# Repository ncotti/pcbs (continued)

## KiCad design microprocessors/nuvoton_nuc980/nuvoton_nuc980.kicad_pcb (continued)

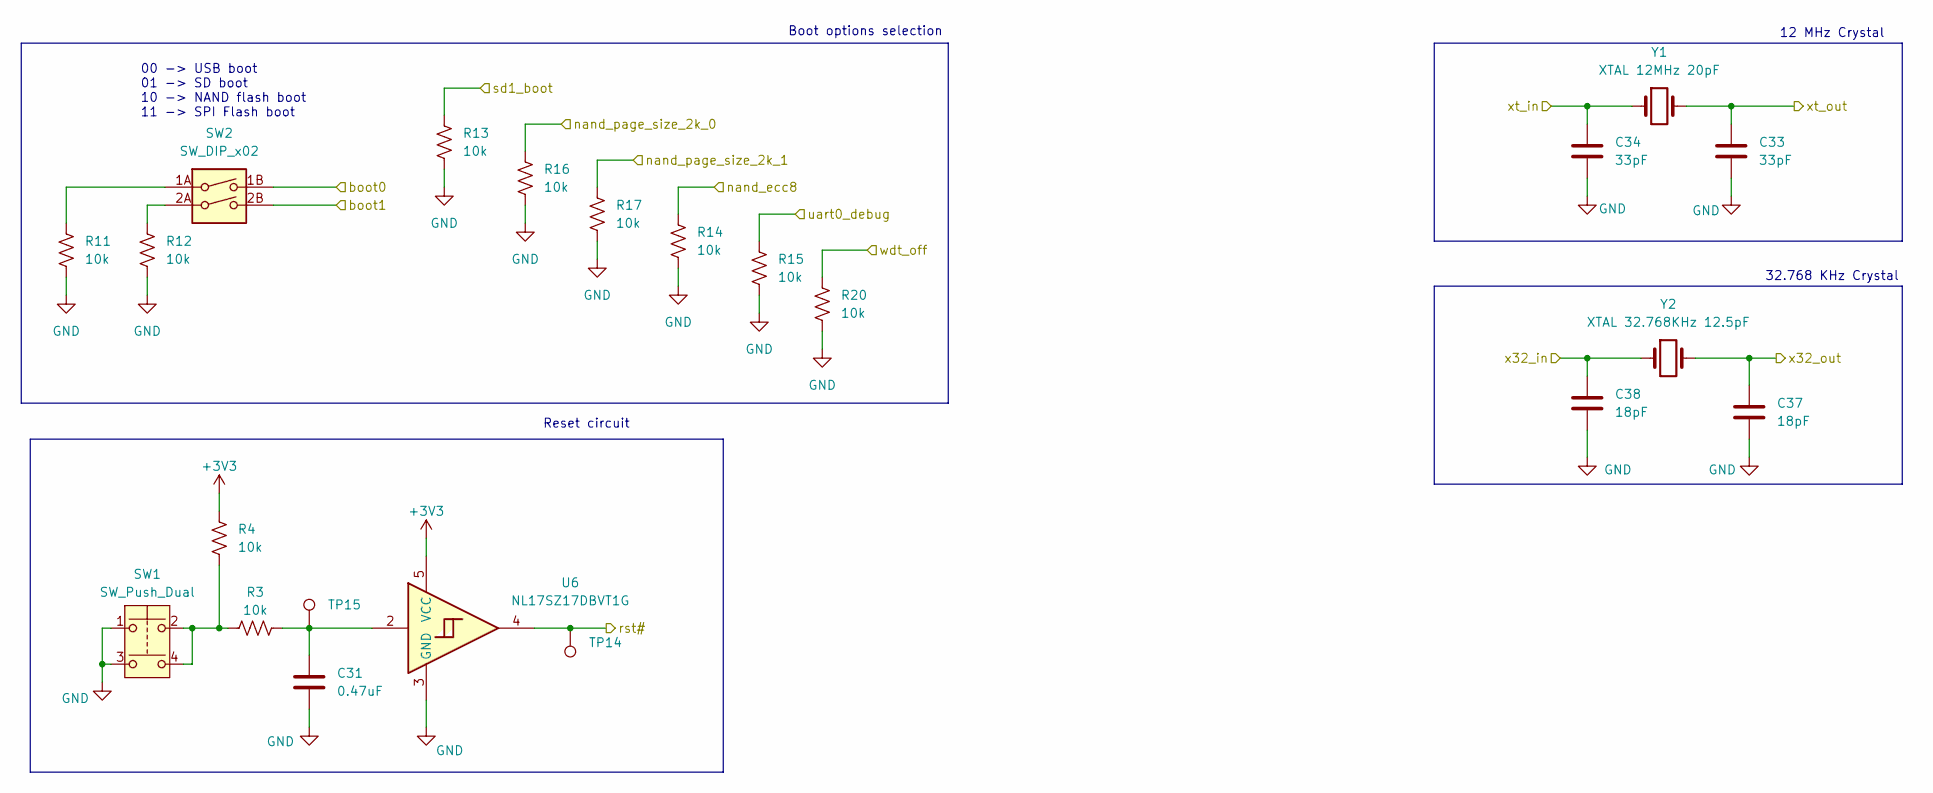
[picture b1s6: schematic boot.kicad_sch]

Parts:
C31: 0.47uF; C_0805_2012Metric_Pad1.18x1.45mm_HandSolder; Mfr. P/N CL21B474KAFNNNG
C33, C34: 33pF; C_0805_2012Metric_Pad1.18x1.45mm_HandSolder; Mfr. P/N CC0805JRNPO9BN330
C37, C38: 18pF; C_0805_2012Metric_Pad1.18x1.45mm_HandSolder; Mfr. P/N CC0805JRNPO9BN180
R3, R4, R11, R12, R13, R14, R15, R16, R17, R20: 10k; R_0805_2012Metric_Pad1.20x1.40mm_HandSolder; Mfr. P/N RC0805FR-1310KL
SW1: SW_Push_Dual; SW_PUSH_6mm_H5mm; Mfr. P/N TS02-66-60-BK-260-SCR-D
SW2: SW_DIP_x02; SW_DS01-254-L-02BE; Mfr. P/N DS01-254-L-02BE
TP14, TP15: TestPoint; TestPoint_Pad_D2.0mm
U6: NL17SZ17DBVT1G; SC-74A-5_1.55x2.9mm_P0.95mm; Mfr. P/N NL17SZ17DBVT1G
Y1: XTAL 12MHz 20pF; Crystal_SMD_HC49-SD_HandSoldering; Mfr. P/N 12M20P2/49SMT
Y2: XTAL 32.768KHz 12.5pF; Crystal_SMD_3215-2Pin_3.2x1.5mm; Mfr. P/N Q 0,032768-JTX310-12,5-20-T2-70K-LF

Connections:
+3V3: R4.1, U6.5 (VCC); also elsewhere on the board
/boot0: SW2.1B; also elsewhere on the board
/boot1: SW2.2B; also elsewhere on the board
/nand_ecc8: R14.1; also elsewhere on the board
/nand_page_size_2k_0: R16.1; also elsewhere on the board
/nand_page_size_2k_1: R17.1; also elsewhere on the board
/rst#: TP14.1, U6.4; also elsewhere on the board
/sd1_boot: R13.1; also elsewhere on the board
/uart0_debug: R15.1; also elsewhere on the board
/wdt_off: R20.1; also elsewhere on the board
/x32_in: C38.1, Y2.1; also elsewhere on the board
/x32_out: C37.1, Y2.2; also elsewhere on the board
/xt_in: C34.1, Y1.1; also elsewhere on the board
/xt_out: C33.1, Y1.2; also elsewhere on the board
GND: C31.2, C33.2, C34.2, C37.2, C38.2, R11.2, R12.2, R13.2, R14.2, R15.2, R16.2, R17.2, R20.2, SW1.1, SW1.3, U6.3 (GND); also elsewhere on the board
unnamed: C31.1, R3.2, TP15.1, U6.2
unnamed: R3.1, R4.2, SW1.2, SW1.4
unnamed: R11.1, SW2.1A
unnamed: R12.1, SW2.2A

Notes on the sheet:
Boot options selection
Reset circuit
00 -> USB boot 01 -> SD boot 10 -> NAND flash boot 11 -> SPI Flash boot
12 MHz Crystal
32.768 KHz Crystal

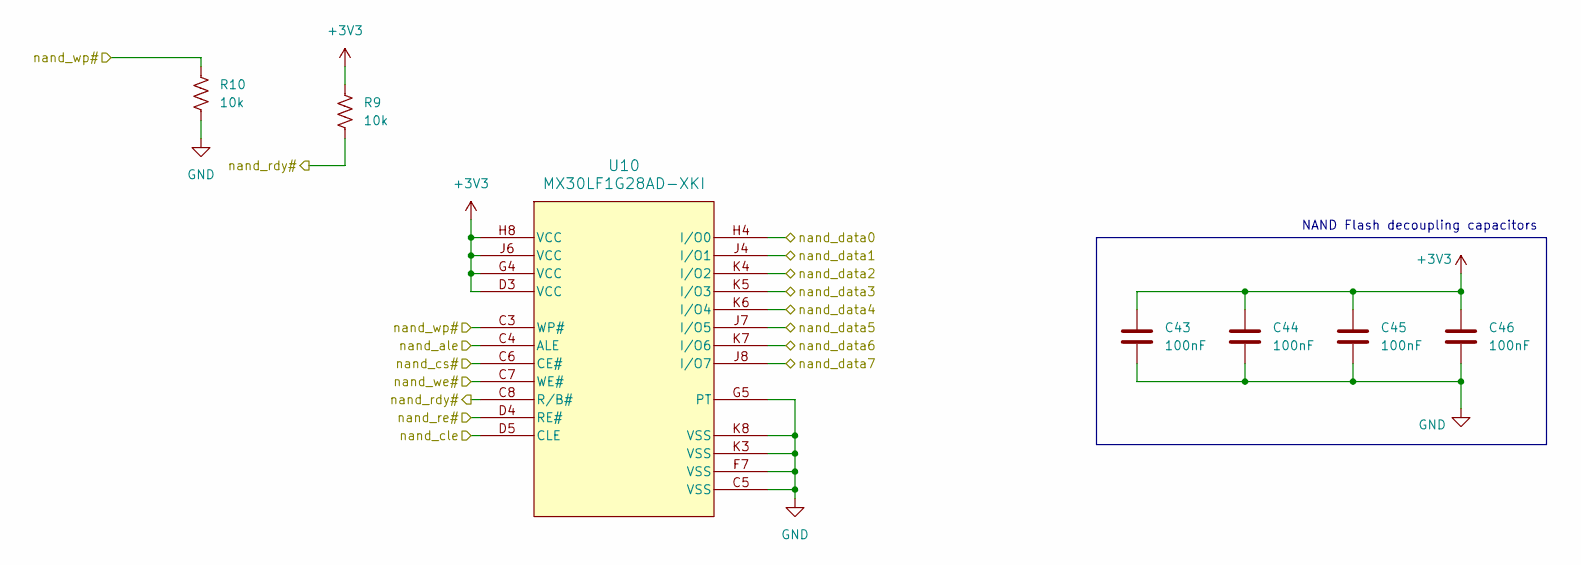
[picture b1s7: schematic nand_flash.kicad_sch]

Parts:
C43, C44, C45, C46: 100nF; C_0805_2012Metric_Pad1.18x1.45mm_HandSolder; Mfr. P/N CL21B104KACNNNC
R9, R10: 10k; R_0805_2012Metric_Pad1.20x1.40mm_HandSolder; Mfr. P/N RC0805FR-1310KL
U10: MX30LF1G28AD-XKI; VFBGA63_9X11_MAC-M; Mfr. P/N MX30LF1G28AD-XKI

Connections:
+3V3: C43.1, C44.1, C45.1, C46.1, R9.1, U10.D3 (VCC), U10.G4 (VCC), U10.H8 (VCC), U10.J6 (VCC); also elsewhere on the board
/nand_ale: U10.C4 (ALE); also elsewhere on the board
/nand_cle: U10.D5 (CLE); also elsewhere on the board
/nand_cs#: U10.C6 (CE#); also elsewhere on the board
/nand_data0: U10.H4 (I/O0); also elsewhere on the board
/nand_data1: U10.J4 (I/O1); also elsewhere on the board
/nand_data2: U10.K4 (I/O2); also elsewhere on the board
/nand_data3: U10.K5 (I/O3); also elsewhere on the board
/nand_data4: U10.K6 (I/O4); also elsewhere on the board
/nand_data5: U10.J7 (I/O5); also elsewhere on the board
/nand_data6: U10.K7 (I/O6); also elsewhere on the board
/nand_data7: U10.J8 (I/O7); also elsewhere on the board
/nand_rdy#: R9.2, U10.C8 (R/B#); also elsewhere on the board
/nand_re#: U10.D4 (RE#); also elsewhere on the board
/nand_we#: U10.C7 (WE#); also elsewhere on the board
/nand_wp#: R10.1, U10.C3 (WP#); also elsewhere on the board
GND: C43.2, C44.2, C45.2, C46.2, R10.2, U10.C5 (VSS), U10.F7 (VSS), U10.G5 (PT), U10.K3 (VSS), U10.K8 (VSS); also elsewhere on the board

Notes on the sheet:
NAND Flash decoupling capacitors

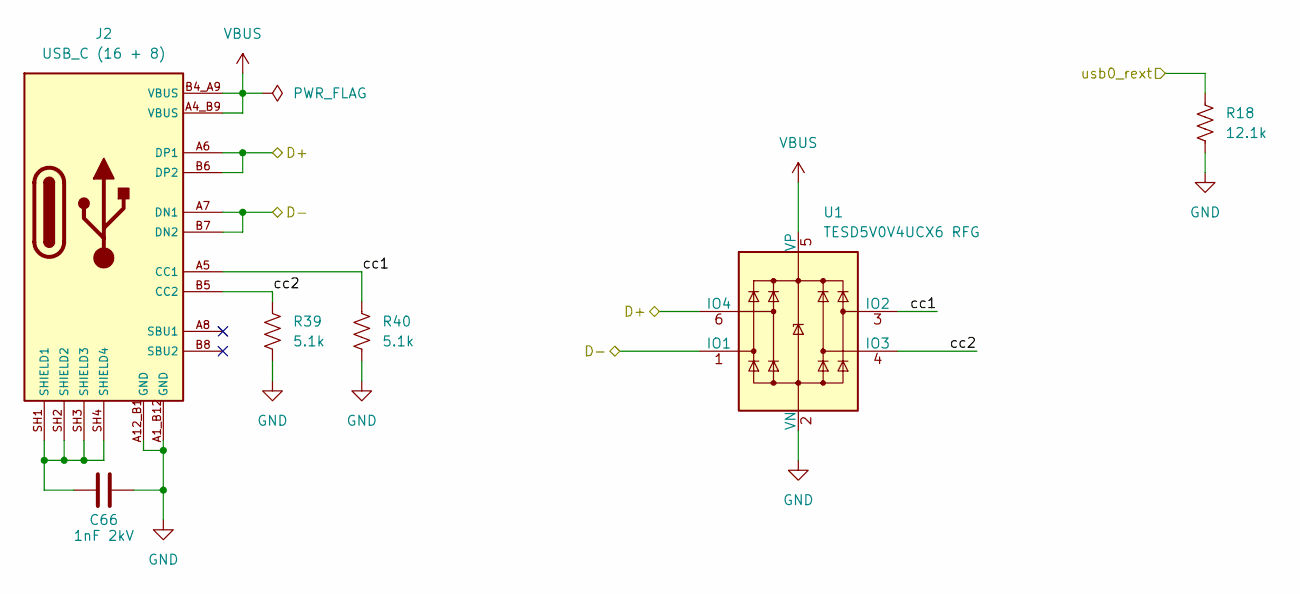
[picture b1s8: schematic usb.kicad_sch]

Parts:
C66: 1nF 2kV; C_1206_3216Metric_Pad1.33x1.80mm_HandSolder; Mfr. P/N 1206B102M202CT
J2: USB_C (16 + 8); SAMESKY_UJ20-C-H-G-SMT-5-P16-TR; Mfr. P/N UJ20-C-H-G-SMT-5-P16-TR
R18: 12.1k; R_0805_2012Metric_Pad1.20x1.40mm_HandSolder; Mfr. P/N AC0805FR-0712K1L
R39, R40: 5.1k; R_0805_2012Metric_Pad1.20x1.40mm_HandSolder; Mfr. P/N RC0805FR-135K1L
U1: TESD5V0V4UCX6 RFG; SOT-23-6; Mfr. P/N TESD5V0V4UCX6 RFG

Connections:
/USB/cc1: J2.A5 (CC1), R40.1, U1.3 (IO2)
/USB/cc2: J2.B5 (CC2), R39.1, U1.4 (IO3)
/usb0_d+: J2.A6 (DP1), J2.B6 (DP2), U1.6 (IO4); also elsewhere on the board
/usb0_d-: J2.A7 (DN1), J2.B7 (DN2), U1.1 (IO1); also elsewhere on the board
/usb0_rext: R18.1; also elsewhere on the board
GND: C66.2, J2.A1_B12 (GND), J2.A12_B1 (GND), R18.2, R39.2, R40.2, U1.2 (VN); also elsewhere on the board
unnamed: C66.1, J2.SH1 (SHIELD1), J2.SH2 (SHIELD2), J2.SH3 (SHIELD3), J2.SH4 (SHIELD4)
VBUS: J2.A4_B9 (VBUS), J2.B4_A9 (VBUS), U1.5 (VP); also elsewhere on the board

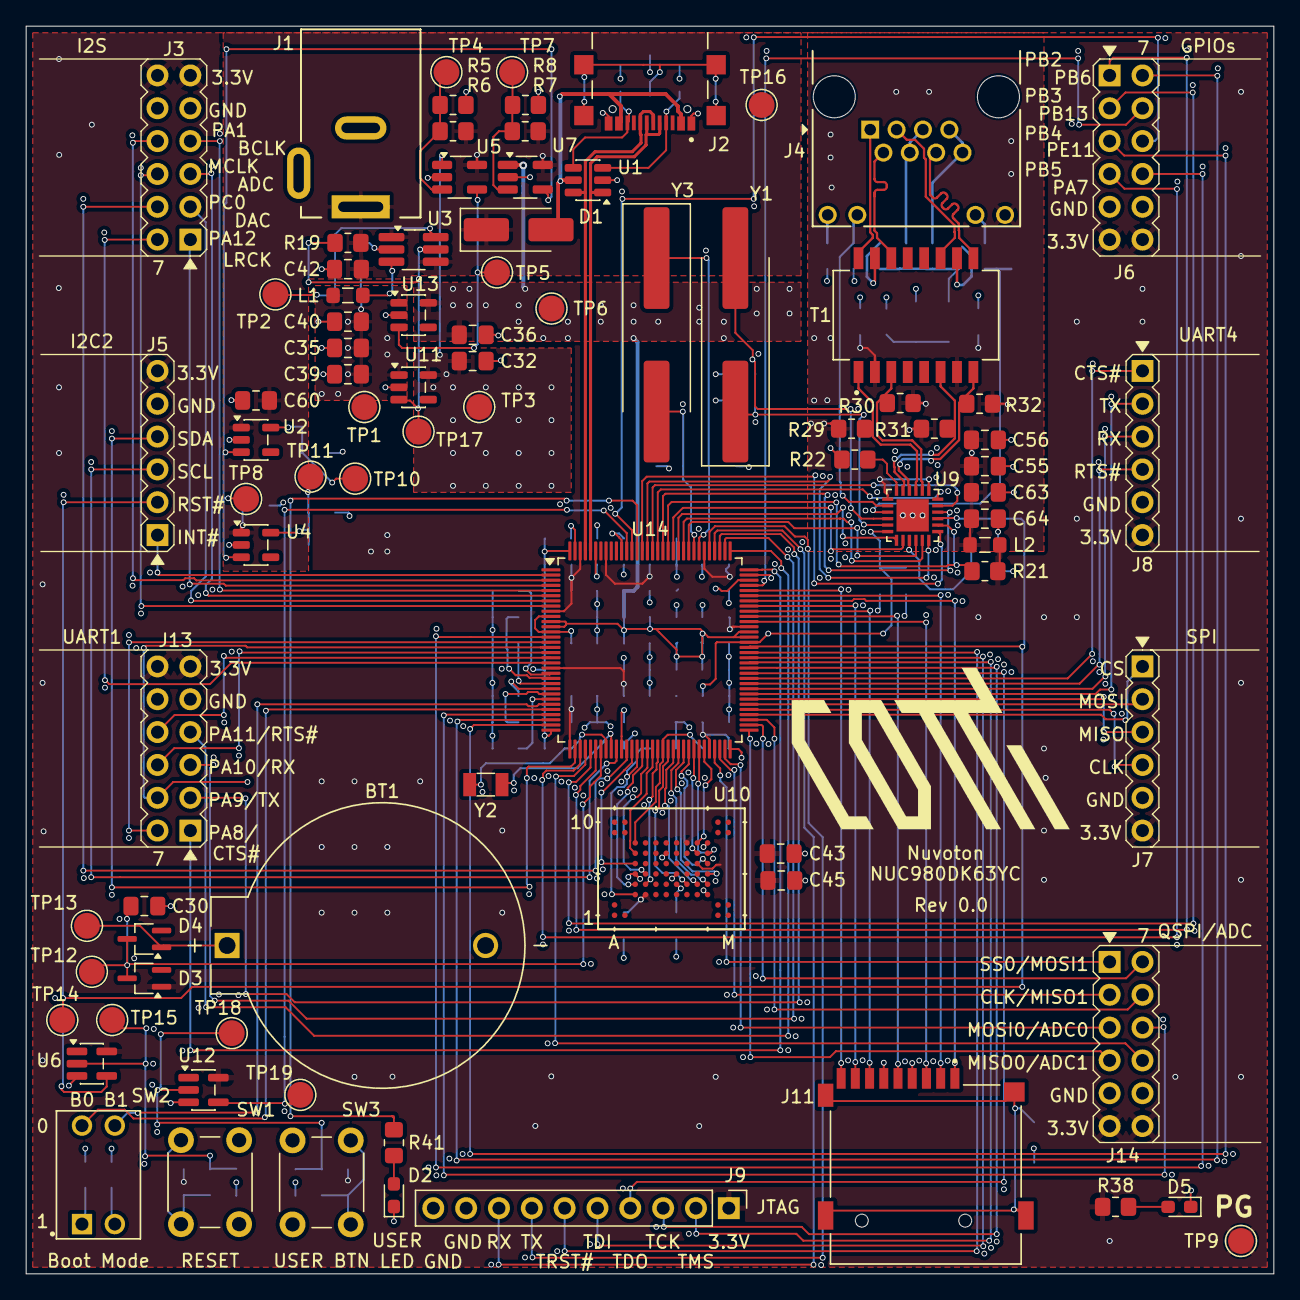
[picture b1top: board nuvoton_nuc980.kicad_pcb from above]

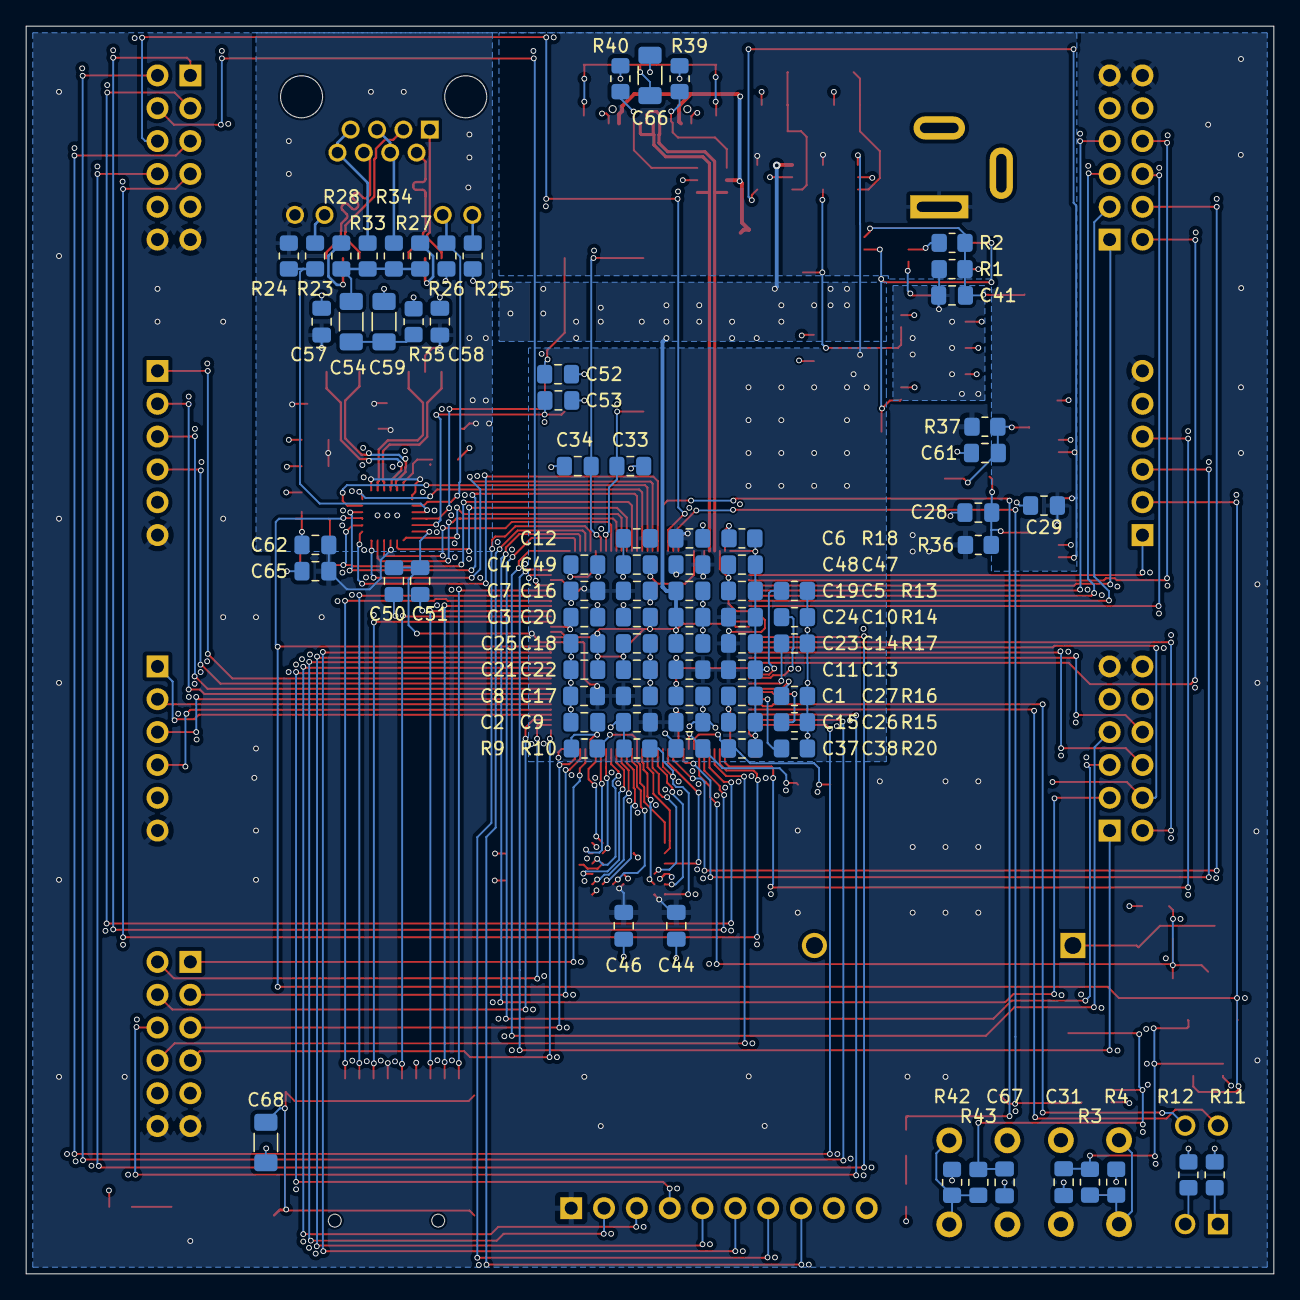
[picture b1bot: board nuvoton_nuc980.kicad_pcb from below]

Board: 4 copper layers, 96.5 x 96.5 mm, 170 parts (84 on the bottom side), 152 nets.

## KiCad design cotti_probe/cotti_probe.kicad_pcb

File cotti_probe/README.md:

# Cotti probe

Cotti probe is a [FT4232H] based probe, compatible with JTAG/SWD/UART/SWO.

<!-- External links -->
[ft4232h]: https://ftdichip.com/products/ft4232hl/

https://digilent.com/reference/_media/jtag_hs2:jtag-hs2_rm.pdf

https://github.com/Neofoxx/JTAG-SWD-adapter

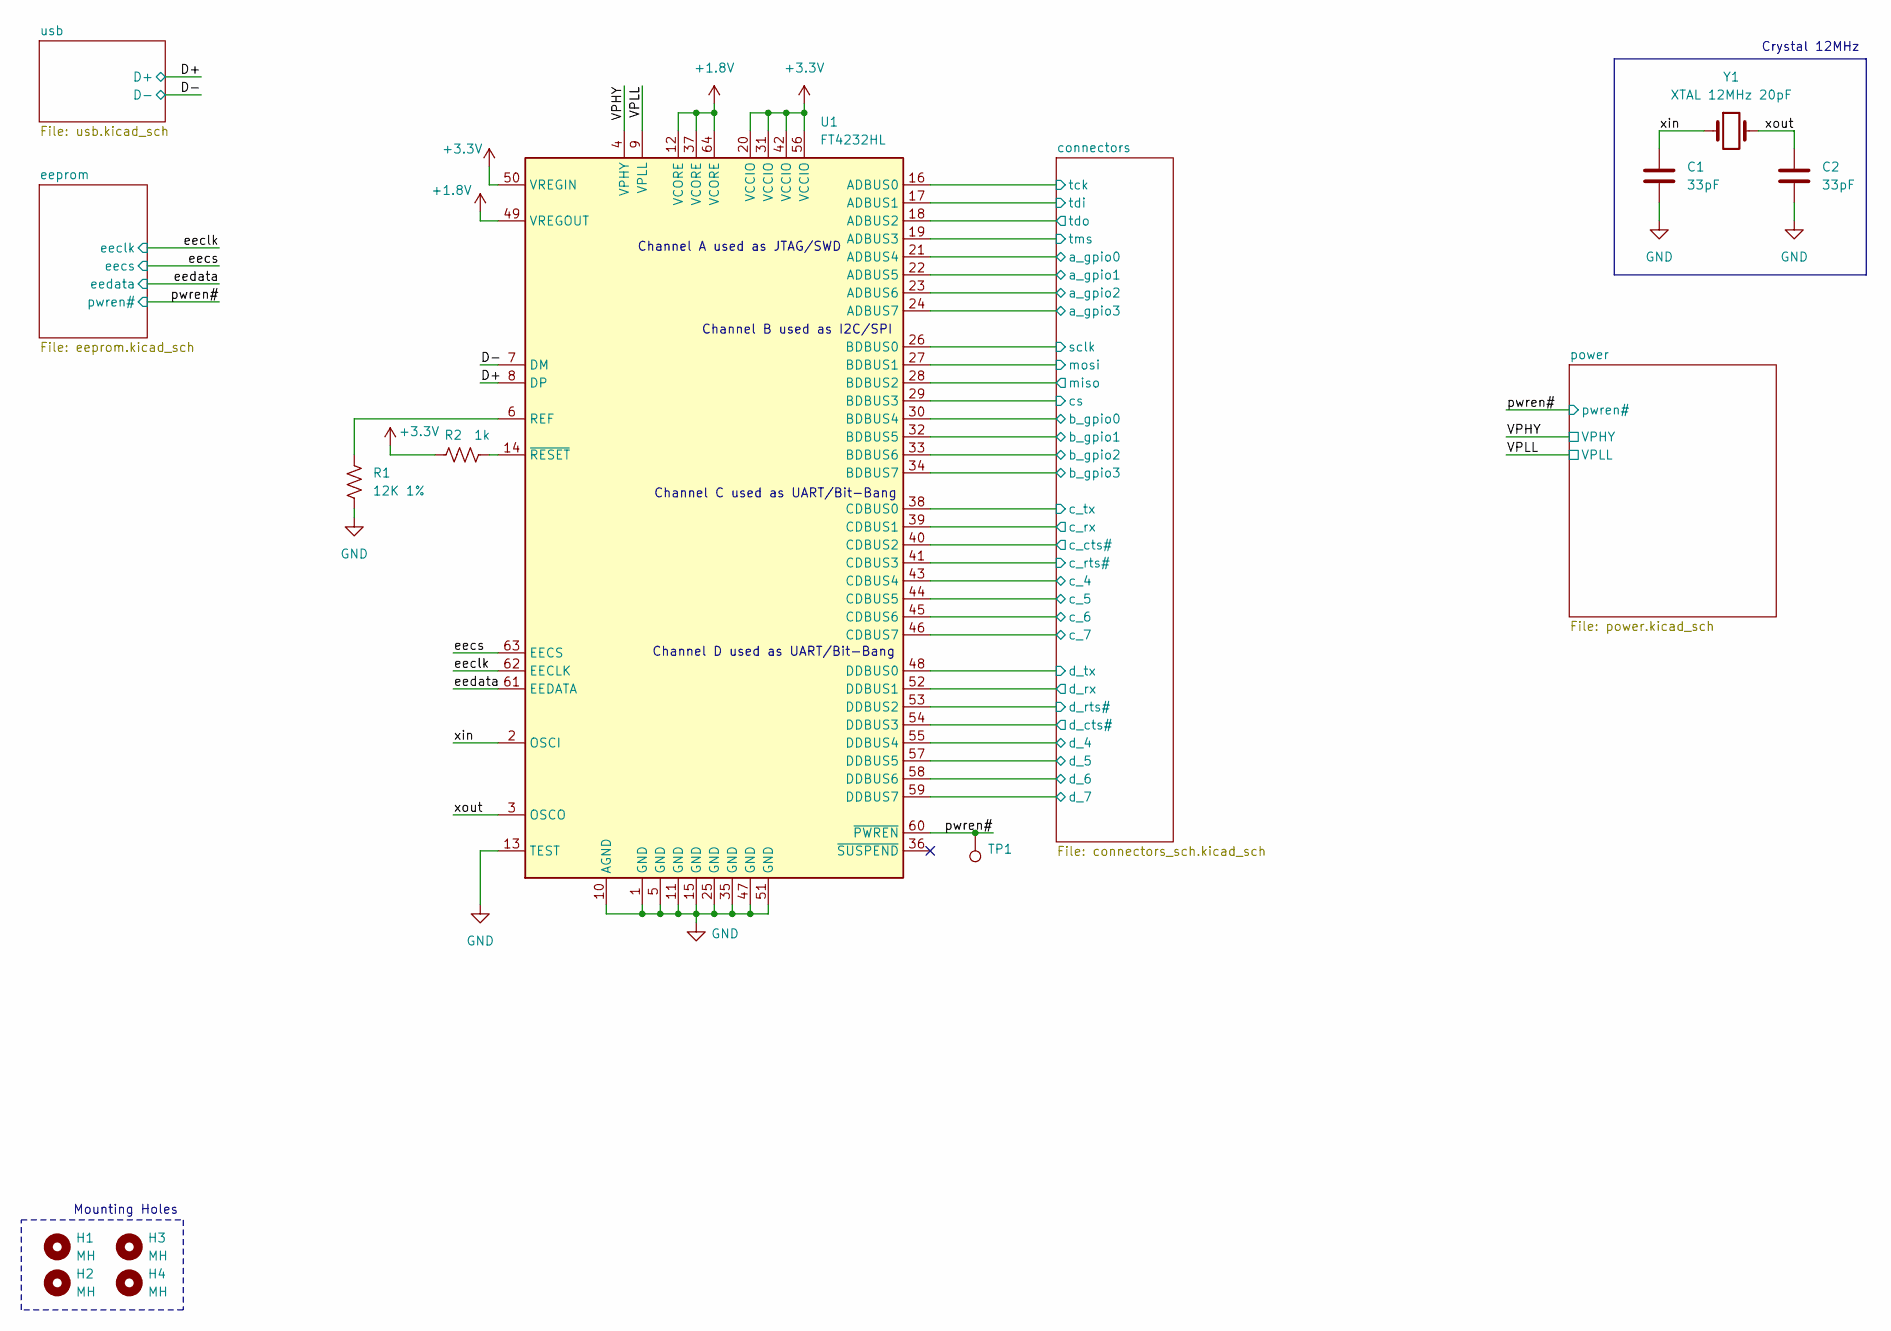
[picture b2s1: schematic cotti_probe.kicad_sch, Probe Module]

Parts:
C1, C2: 33pF; C_0805_2012Metric_Pad1.18x1.45mm_HandSolder; Mfr. P/N CC0805JRNPO9BN330
H1, H2, H3, H4: MH; MountingHole_2.2mm_M2_ISO14580
R1: 12K 1%; R_0805_2012Metric_Pad1.20x1.40mm_HandSolder; Mfr. P/N RC0805FR-1012KL
R2: 1k; R_0805_2012Metric_Pad1.20x1.40mm_HandSolder; Mfr. P/N RC0805FR-071KL
TP1: TestPoint; TestPoint_Pad_D2.0mm
U1: FT4232HL; LQFP-64_10x10mm_P0.5mm; Mfr. P/N FT4232HL-REEL
Y1: XTAL 12MHz 20pF; Crystal_SMD_HC49-SD_HandSoldering; Mfr. P/N 12M20P2/49SMT

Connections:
+1.8V: U1.12 (VCORE), U1.37 (VCORE), U1.49 (VREGOUT), U1.64 (VCORE); also elsewhere on the board
+3.3V: R2.1, U1.20 (VCCIO), U1.31 (VCCIO), U1.42 (VCCIO), U1.50 (VREGIN), U1.56 (VCCIO); also elsewhere on the board
/D+: U1.8 (DP); also elsewhere on the board
/D-: U1.7 (DM); also elsewhere on the board
/VPHY: U1.4 (VPHY); also elsewhere on the board
/VPLL: U1.9 (VPLL); also elsewhere on the board
/connectors/a_gpio0: U1.21 (ADBUS4); also elsewhere on the board
/connectors/a_gpio1: U1.22 (ADBUS5); also elsewhere on the board
/connectors/a_gpio2: U1.23 (ADBUS6); also elsewhere on the board
/connectors/a_gpio3: U1.24 (ADBUS7); also elsewhere on the board
/connectors/b_gpio0: U1.30 (BDBUS4); also elsewhere on the board
/connectors/b_gpio1: U1.32 (BDBUS5); also elsewhere on the board
/connectors/b_gpio2: U1.33 (BDBUS6); also elsewhere on the board
/connectors/b_gpio3: U1.34 (BDBUS7); also elsewhere on the board
/connectors/c_4: U1.43 (CDBUS4); also elsewhere on the board
/connectors/c_5: U1.44 (CDBUS5); also elsewhere on the board
/connectors/c_6: U1.45 (CDBUS6); also elsewhere on the board
/connectors/c_7: U1.46 (CDBUS7); also elsewhere on the board
/connectors/c_cts#: U1.40 (CDBUS2); also elsewhere on the board
/connectors/c_rts#: U1.41 (CDBUS3); also elsewhere on the board
/connectors/c_rx: U1.39 (CDBUS1); also elsewhere on the board
/connectors/c_tx: U1.38 (CDBUS0); also elsewhere on the board
/connectors/cs: U1.29 (BDBUS3); also elsewhere on the board
/connectors/d_4: U1.55 (DDBUS4); also elsewhere on the board
/connectors/d_5: U1.57 (DDBUS5); also elsewhere on the board
/connectors/d_6: U1.58 (DDBUS6); also elsewhere on the board
/connectors/d_7: U1.59 (DDBUS7); also elsewhere on the board
/connectors/d_cts#: U1.54 (DDBUS3); also elsewhere on the board
/connectors/d_rts#: U1.53 (DDBUS2); also elsewhere on the board
/connectors/d_rx: U1.52 (DDBUS1); also elsewhere on the board
/connectors/d_tx: U1.48 (DDBUS0); also elsewhere on the board
/connectors/miso: U1.28 (BDBUS2); also elsewhere on the board
/connectors/mosi: U1.27 (BDBUS1); also elsewhere on the board
/connectors/sclk: U1.26 (BDBUS0); also elsewhere on the board
/connectors/tck: U1.16 (ADBUS0); also elsewhere on the board
/connectors/tdi: U1.17 (ADBUS1); also elsewhere on the board
/connectors/tdo: U1.18 (ADBUS2); also elsewhere on the board
/connectors/tms: U1.19 (ADBUS3); also elsewhere on the board
/eeclk: U1.62 (EECLK); also elsewhere on the board
/eecs: U1.63 (EECS); also elsewhere on the board
/eedata: U1.61 (EEDATA); also elsewhere on the board
/pwren#: TP1.1, U1.60 (~PWREN); also elsewhere on the board
/xin: C1.1, U1.2 (OSCI), Y1.1
/xout: C2.1, U1.3 (OSCO), Y1.2
GND: C1.2, C2.2, R1.2, U1.1 (GND), U1.5 (GND), U1.10 (AGND), U1.11 (GND), U1.13 (TEST), U1.15 (GND), U1.25 (GND), U1.35 (GND), U1.47 (GND), U1.51 (GND); also elsewhere on the board
unnamed: R1.1, U1.6 (REF)
unnamed: R2.2, U1.14 (~RESET)

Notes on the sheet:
Channel C used as UART/Bit-Bang
Mounting Holes
Channel D used as UART/Bit-Bang
Crystal 12MHz
Channel A used as JTAG/SWD
Channel B used as I2C/SPI

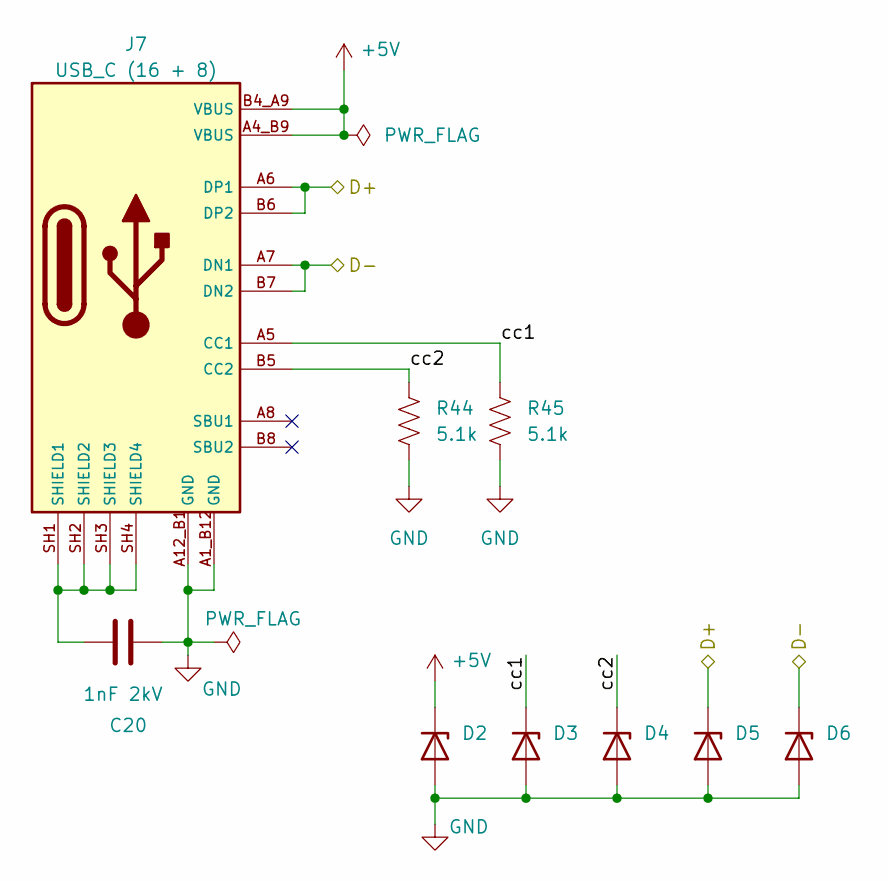
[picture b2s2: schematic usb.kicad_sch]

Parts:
C20: 1nF 2kV; C_1206_3216Metric_Pad1.33x1.80mm_HandSolder; Mfr. P/N 1206B102M202CT
D2, D3, D4, D5, D6: D5V0F1U2LP-7B; D_SOD-523; Mfr. P/N D5V0F1U2LP-7B
J7: USB_C (16 + 8); SAMESKY_UJ20-C-H-G-SMT-5-P16-TR; Mfr. P/N UJ20-C-H-G-SMT-5-P16-TR
R44, R45: 5.1k; R_0805_2012Metric_Pad1.20x1.40mm_HandSolder; Mfr. P/N RC0805FR-135K1L

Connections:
+5V: D2.1 (K), J7.A4_B9 (VBUS), J7.B4_A9 (VBUS); also elsewhere on the board
/D+: D5.1 (K), J7.A6 (DP1), J7.B6 (DP2); also elsewhere on the board
/D-: D6.1 (K), J7.A7 (DN1), J7.B7 (DN2); also elsewhere on the board
/usb/cc1: D3.1 (K), J7.A5 (CC1), R45.1
/usb/cc2: D4.1 (K), J7.B5 (CC2), R44.1
GND: C20.2, D2.2 (A), D3.2 (A), D4.2 (A), D5.2 (A), D6.2 (A), J7.A1_B12 (GND), J7.A12_B1 (GND), R44.2, R45.2; also elsewhere on the board
unnamed: C20.1, J7.SH1 (SHIELD1), J7.SH2 (SHIELD2), J7.SH3 (SHIELD3), J7.SH4 (SHIELD4)

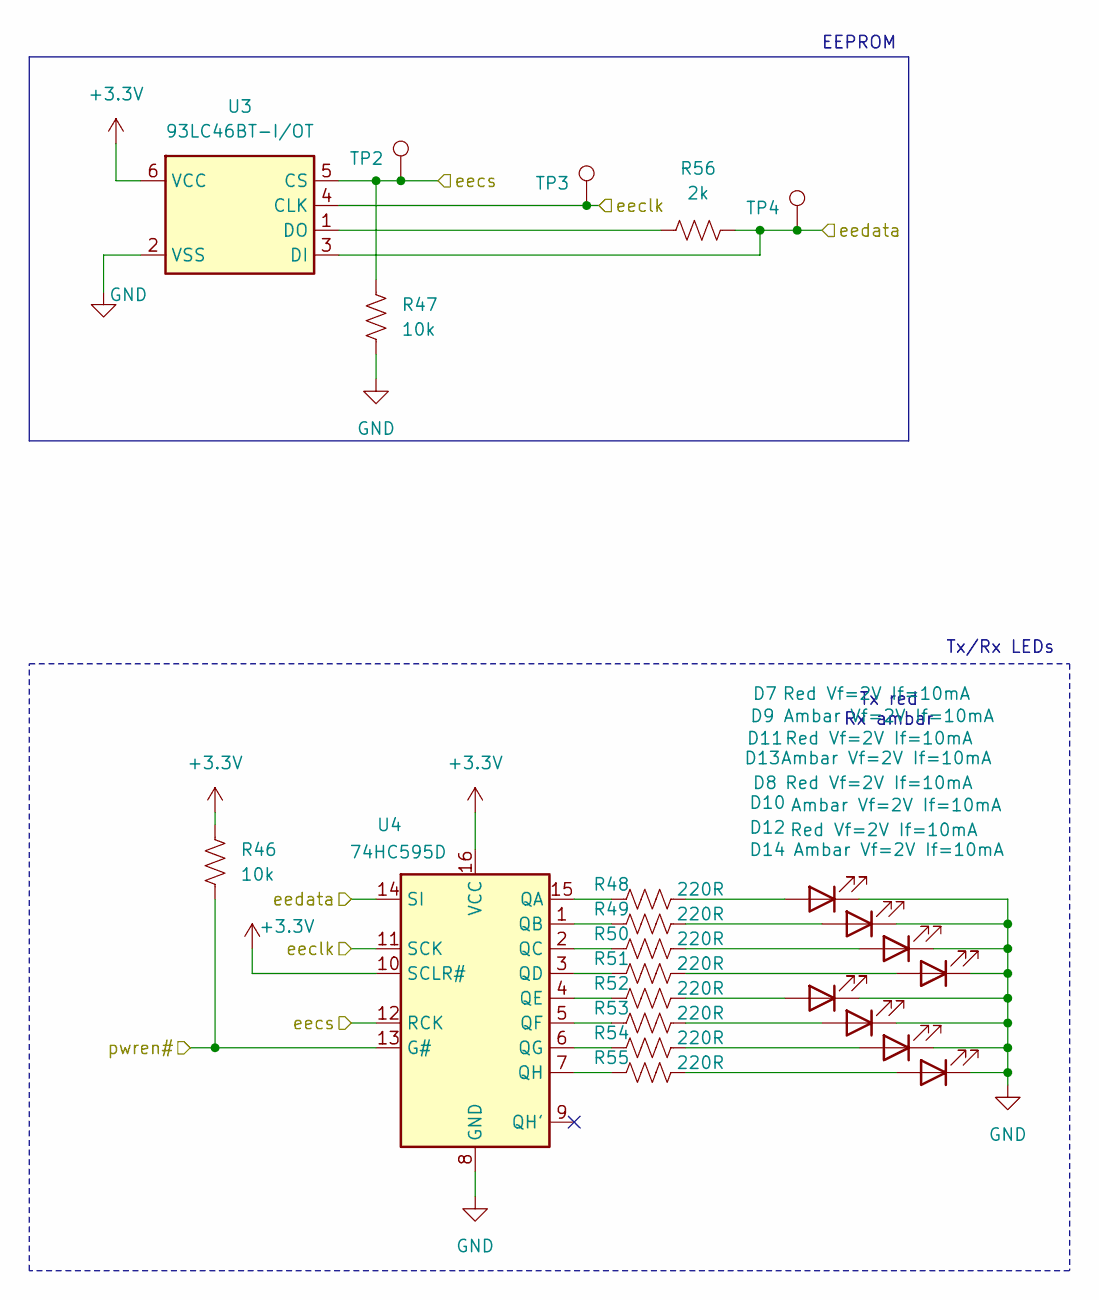
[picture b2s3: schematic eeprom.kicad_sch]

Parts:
D7, D8, D11, D12: Red Vf=2V If=10mA; LED_0603_1608Metric_Pad1.05x0.95mm_HandSolder; Mfr. P/N B1911USD-20D000114U1930
D9, D10, D13, D14: Ambar Vf=2V If=10mA; LED_0603_1608Metric_Pad1.05x0.95mm_HandSolder; Mfr. P/N B1931UY--20D000114U1930
R46, R47: 10k; R_0805_2012Metric_Pad1.20x1.40mm_HandSolder; Mfr. P/N RC0805FR-1310KL
R48, R49, R50, R51, R52, R53, R54, R55: 220R; R_0805_2012Metric_Pad1.20x1.40mm_HandSolder; Mfr. P/N RC0805FR-13220RL
R56: 2k; R_0805_2012Metric_Pad1.20x1.40mm_HandSolder; Mfr. P/N RC0805FR-072KL
TP2, TP3, TP4: TestPoint; TestPoint_Pad_D2.0mm
U3: 93LC46BT-I/OT; SOT-23-6_Handsoldering; Mfr. P/N 93LC46BT-I/OT
U4: 74HC595D; SOIC-16_3.9x9.9mm_P1.27mm; Mfr. P/N 74HC595D

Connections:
+3.3V: R46.1, U3.6 (VCC), U4.10 (SCLR#), U4.16 (VCC); also elsewhere on the board
/eeclk: TP3.1, U3.4 (CLK), U4.11 (SCK); also elsewhere on the board
/eecs: R47.1, TP2.1, U3.5 (CS), U4.12 (RCK); also elsewhere on the board
/eedata: R56.2, TP4.1, U3.3 (DI), U4.14 (SI); also elsewhere on the board
/pwren#: R46.2, U4.13 (G#); also elsewhere on the board
GND: D7.1 (K), D8.1 (K), D9.1 (K), D10.1 (K), D11.1 (K), D12.1 (K), D13.1 (K), D14.1 (K), R47.2, U3.2 (VSS), U4.8 (GND); also elsewhere on the board
unnamed: D7.2 (A), R48.2
unnamed: D8.2 (A), R52.2
unnamed: D9.2 (A), R49.2
unnamed: D10.2 (A), R53.2
unnamed: D11.2 (A), R50.2
unnamed: D12.2 (A), R54.2
unnamed: D13.2 (A), R51.2
unnamed: D14.2 (A), R55.2
unnamed: R56.1, U3.1 (DO)
unnamed: R48.1, U4.15 (QA)
unnamed: R49.1, U4.1 (QB)
unnamed: R50.1, U4.2 (QC)
unnamed: R51.1, U4.3 (QD)
unnamed: R52.1, U4.4 (QE)
unnamed: R53.1, U4.5 (QF)
unnamed: R54.1, U4.6 (QG)
unnamed: R55.1, U4.7 (QH)

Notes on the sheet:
EEPROM
Tx red Rx ambar
Tx/Rx LEDs

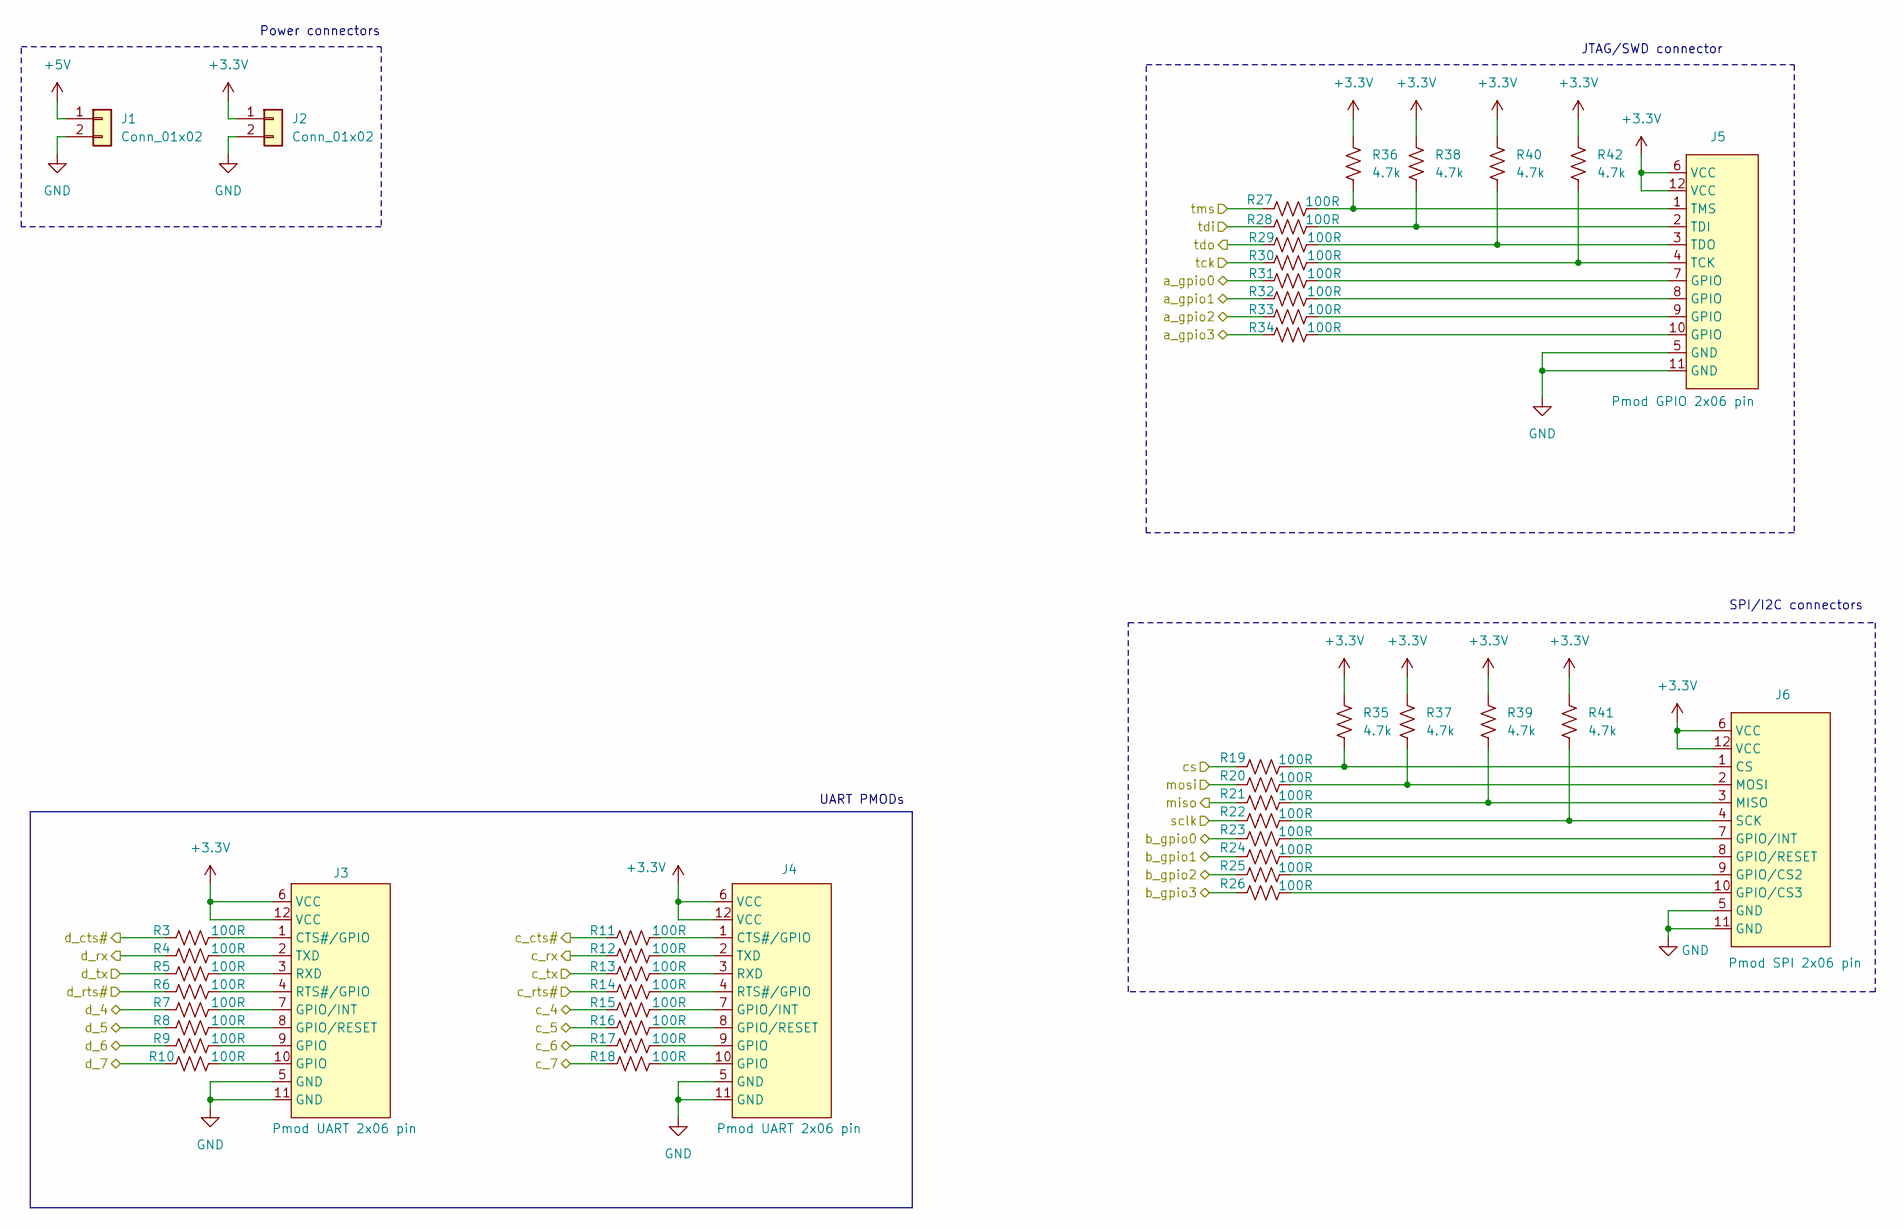
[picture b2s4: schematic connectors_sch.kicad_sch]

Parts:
J1, J2: Conn_01x02; PinHeader_1x02_P2.54mm_Vertical
J3, J4: Pmod UART 2x06 pin; Pmod_2x06_pin; Mfr. P/N PH2RA-12-UA
J5: Pmod GPIO 2x06 pin; Pmod_2x06_pin; Mfr. P/N PH2RA-12-UA
J6: Pmod SPI 2x06 pin; Pmod_2x06_pin; Mfr. P/N PH2RA-12-UA
R3, R4, R5, R6, R7, R8, R9, R10, R11, R12, R13, R14, R15, R16, R17, R18, R19, R20, R21, R22, R23, R24, R25, R26, R27, R28, R29, R30, R31, R32, R33, R34: 100R; R_0805_2012Metric_Pad1.20x1.40mm_HandSolder; Mfr. P/N RC0805FR-10100RL
R35, R36, R37, R38, R39, R40, R41, R42: 4.7k; R_0805_2012Metric_Pad1.20x1.40mm_HandSolder; Mfr. P/N RC0805FR-134K7L

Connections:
+3.3V: J2.1, J3.6 (VCC), J3.12 (VCC), J4.6 (VCC), J4.12 (VCC), J5.6 (VCC), J5.12 (VCC), J6.6 (VCC), J6.12 (VCC), R35.1, R36.1, R37.1, R38.1, R39.1, R40.1, R41.1, R42.1; also elsewhere on the board
+5V: J1.1; also elsewhere on the board
/connectors/a_gpio0: R31.1; also elsewhere on the board
/connectors/a_gpio1: R32.1; also elsewhere on the board
/connectors/a_gpio2: R33.1; also elsewhere on the board
/connectors/a_gpio3: R34.1; also elsewhere on the board
/connectors/b_gpio0: R23.1; also elsewhere on the board
/connectors/b_gpio1: R24.1; also elsewhere on the board
/connectors/b_gpio2: R25.1; also elsewhere on the board
/connectors/b_gpio3: R26.1; also elsewhere on the board
/connectors/c_4: R15.1; also elsewhere on the board
/connectors/c_5: R16.1; also elsewhere on the board
/connectors/c_6: R17.1; also elsewhere on the board
/connectors/c_7: R18.1; also elsewhere on the board
/connectors/c_cts#: R11.1; also elsewhere on the board
/connectors/c_rts#: R14.1; also elsewhere on the board
/connectors/c_rx: R12.1; also elsewhere on the board
/connectors/c_tx: R13.1; also elsewhere on the board
/connectors/cs: R19.1; also elsewhere on the board
/connectors/d_4: R7.1; also elsewhere on the board
/connectors/d_5: R8.1; also elsewhere on the board
/connectors/d_6: R9.1; also elsewhere on the board
/connectors/d_7: R10.1; also elsewhere on the board
/connectors/d_cts#: R3.1; also elsewhere on the board
/connectors/d_rts#: R6.1; also elsewhere on the board
/connectors/d_rx: R4.1; also elsewhere on the board
/connectors/d_tx: R5.1; also elsewhere on the board
/connectors/miso: R21.1; also elsewhere on the board
/connectors/mosi: R20.1; also elsewhere on the board
/connectors/sclk: R22.1; also elsewhere on the board
/connectors/tck: R30.1; also elsewhere on the board
/connectors/tdi: R28.1; also elsewhere on the board
/connectors/tdo: R29.1; also elsewhere on the board
/connectors/tms: R27.1; also elsewhere on the board
GND: J1.2, J2.2, J3.5 (GND), J3.11 (GND), J4.5 (GND), J4.11 (GND), J5.5 (GND), J5.11 (GND), J6.5 (GND), J6.11 (GND); also elsewhere on the board
unnamed: J3.1 (CTS#/GPIO), R3.2
unnamed: J3.9 (GPIO), R9.2
unnamed: J3.10 (GPIO), R10.2
unnamed: J3.7 (GPIO/INT), R7.2
unnamed: J3.8 (GPIO/RESET), R8.2
unnamed: J3.4 (RTS#/GPIO), R6.2
unnamed: J3.3 (RXD), R5.2
unnamed: J3.2 (TXD), R4.2
unnamed: J4.1 (CTS#/GPIO), R11.2
unnamed: J4.9 (GPIO), R17.2
unnamed: J4.10 (GPIO), R18.2
unnamed: J4.7 (GPIO/INT), R15.2
unnamed: J4.8 (GPIO/RESET), R16.2
unnamed: J4.4 (RTS#/GPIO), R14.2
unnamed: J4.3 (RXD), R13.2
unnamed: J4.2 (TXD), R12.2
unnamed: J5.7 (GPIO), R31.2
unnamed: J5.8 (GPIO), R32.2
unnamed: J5.9 (GPIO), R33.2
unnamed: J5.10 (GPIO), R34.2
unnamed: J5.4 (TCK), R30.2, R42.2
unnamed: J5.2 (TDI), R28.2, R38.2
unnamed: J5.3 (TDO), R29.2, R40.2
unnamed: J5.1 (TMS), R27.2, R36.2
unnamed: J6.1 (CS), R19.2, R35.2
unnamed: J6.9 (GPIO/CS2), R25.2
unnamed: J6.10 (GPIO/CS3), R26.2
unnamed: J6.7 (GPIO/INT), R23.2
unnamed: J6.8 (GPIO/RESET), R24.2
unnamed: J6.3 (MISO), R21.2, R39.2
unnamed: J6.2 (MOSI), R20.2, R37.2
unnamed: J6.4 (SCK), R22.2, R41.2

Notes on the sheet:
SPI/I2C connectors
UART PMODs
JTAG/SWD connector
Power connectors
